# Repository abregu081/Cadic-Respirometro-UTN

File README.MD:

# Control Respirometro

## Notas
1. Se agrego el primer diseño de la PCB
2. Se presenta la version 1.0 de la app de cotrol grafica
3. Contiene el codigo del microcontrolar dentro del mismo repositorio "scr/"

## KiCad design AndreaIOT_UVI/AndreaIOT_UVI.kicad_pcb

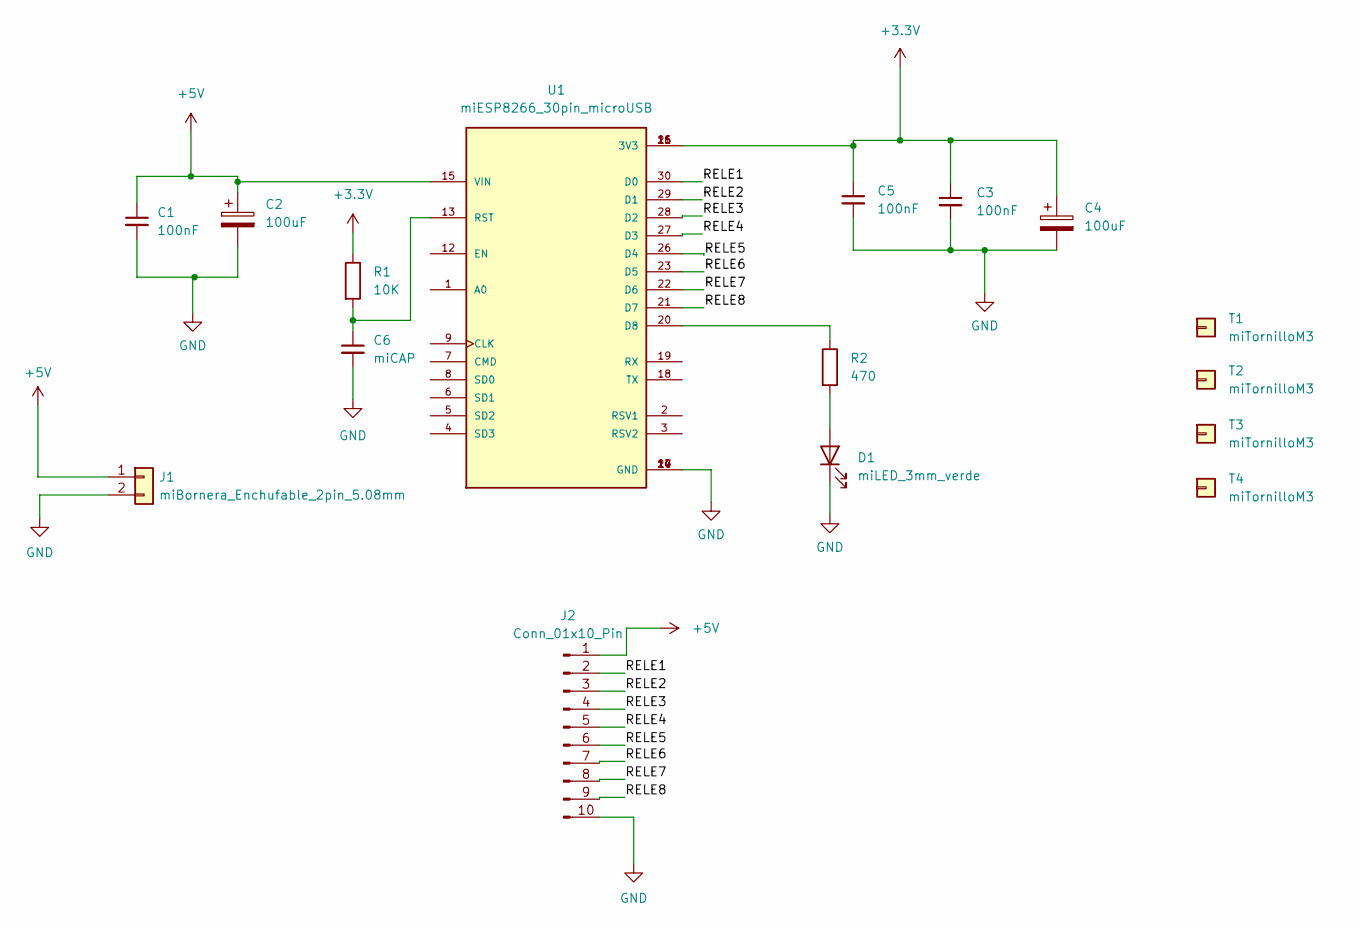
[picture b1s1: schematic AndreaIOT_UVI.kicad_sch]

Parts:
C1, C3, C5: 100nF; miCAP_lenteja_p4mm
C2, C4: 100uF; miCP_vertical_D5.0mm_P2.5mm
C6: miCAP; miCAP_lenteja_p4mm
D1: miLED_3mm_verde; miLED_D3.0mm_verde
J1: miBornera_Enchufable_2pin_5.08mm; miBornera_enchufable_2pin_p5.08mm
J2: Conn_01x10_Pin; Molex_KK-254_AE-6410-10A_1x10_P2.54mm_Vertical
R1: 10K; miRES_0.25W_D1.6mm_P2.54mm_Vertical
R2: 470; miRES_0.25W_D1.6mm_P2.54mm_Vertical
T1, T2, T3, T4: miTornilloM3; M3
U1: miESP8266_30pin_microUSB; miESP8266_30pin; PARTREV 1.0

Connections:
+3.3V: C3.1, C4.1, C5.1, R1.1, U1.11 (3V3), U1.16 (3V3), U1.25 (3V3)
+5V: C1.1, C2.1, J1.1, J2.1, U1.15 (VIN)
/RELE1: J2.2, U1.30 (D0)
/RELE2: J2.3, U1.29 (D1)
/RELE3: J2.4, U1.28 (D2)
/RELE4: J2.5, U1.27 (D3)
/RELE5: J2.6, U1.26 (D4)
/RELE6: J2.7, U1.23 (D5)
/RELE7: J2.8, U1.22 (D6)
/RELE8: J2.9, U1.21 (D7)
GND: C1.2, C2.2, C3.2, C4.2, C5.2, C6.2, D1.1 (K), J1.2, J2.10, U1.10 (GND), U1.14 (GND), U1.17 (GND), U1.24 (GND)
unnamed: D1.2 (A), R2.2
unnamed: R2.1, U1.20 (D8)
unnamed: C6.1, R1.2, U1.13 (RST)

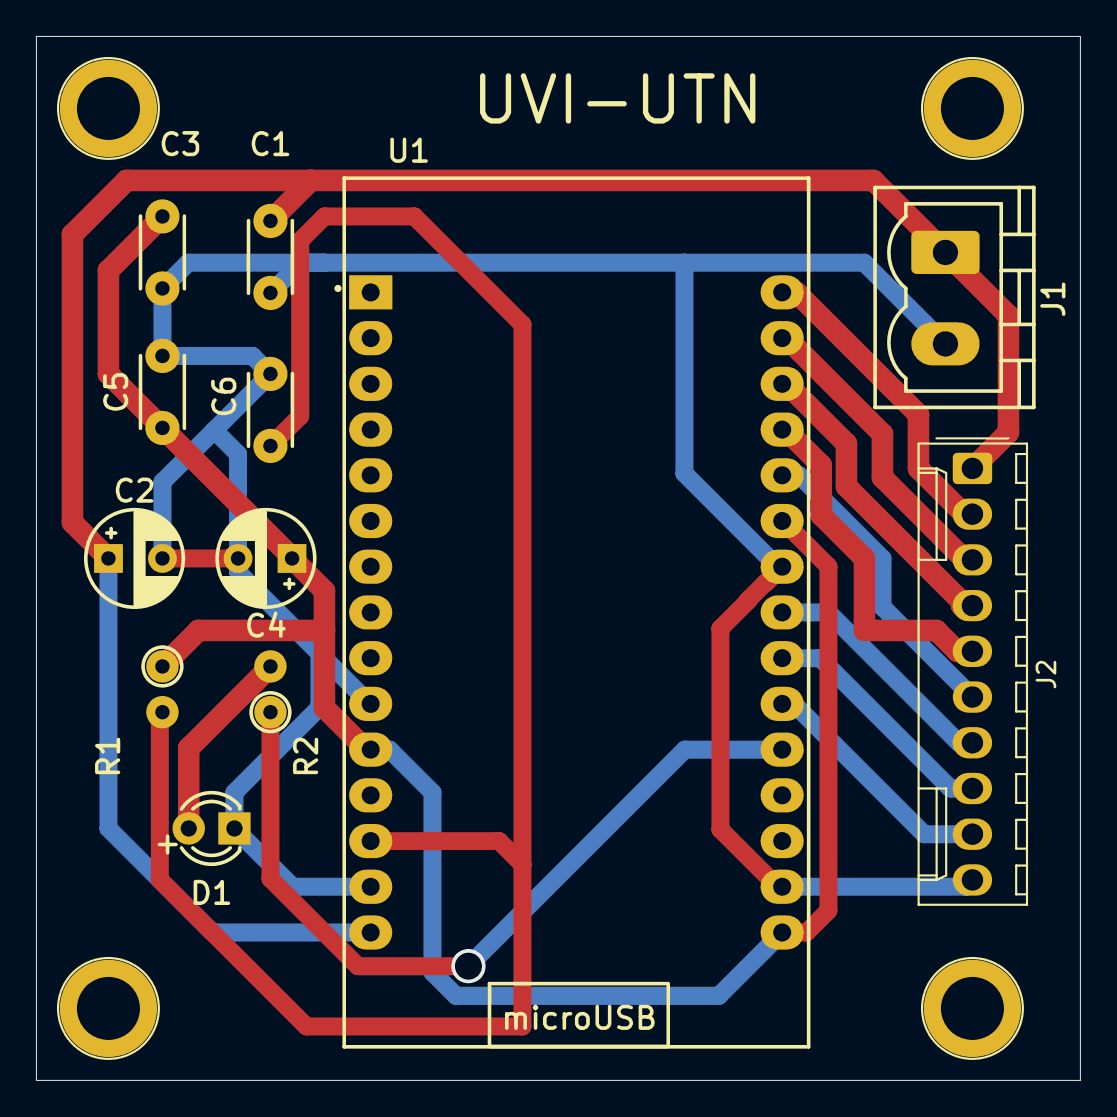
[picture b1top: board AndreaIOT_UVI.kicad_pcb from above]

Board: 2 copper layers, 58.0 x 58.0 mm, 16 parts (0 on the bottom side), 14 nets.

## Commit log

2025-12-29 Version Estable 1.0
2026-01-07 PCB y Esquematicos
